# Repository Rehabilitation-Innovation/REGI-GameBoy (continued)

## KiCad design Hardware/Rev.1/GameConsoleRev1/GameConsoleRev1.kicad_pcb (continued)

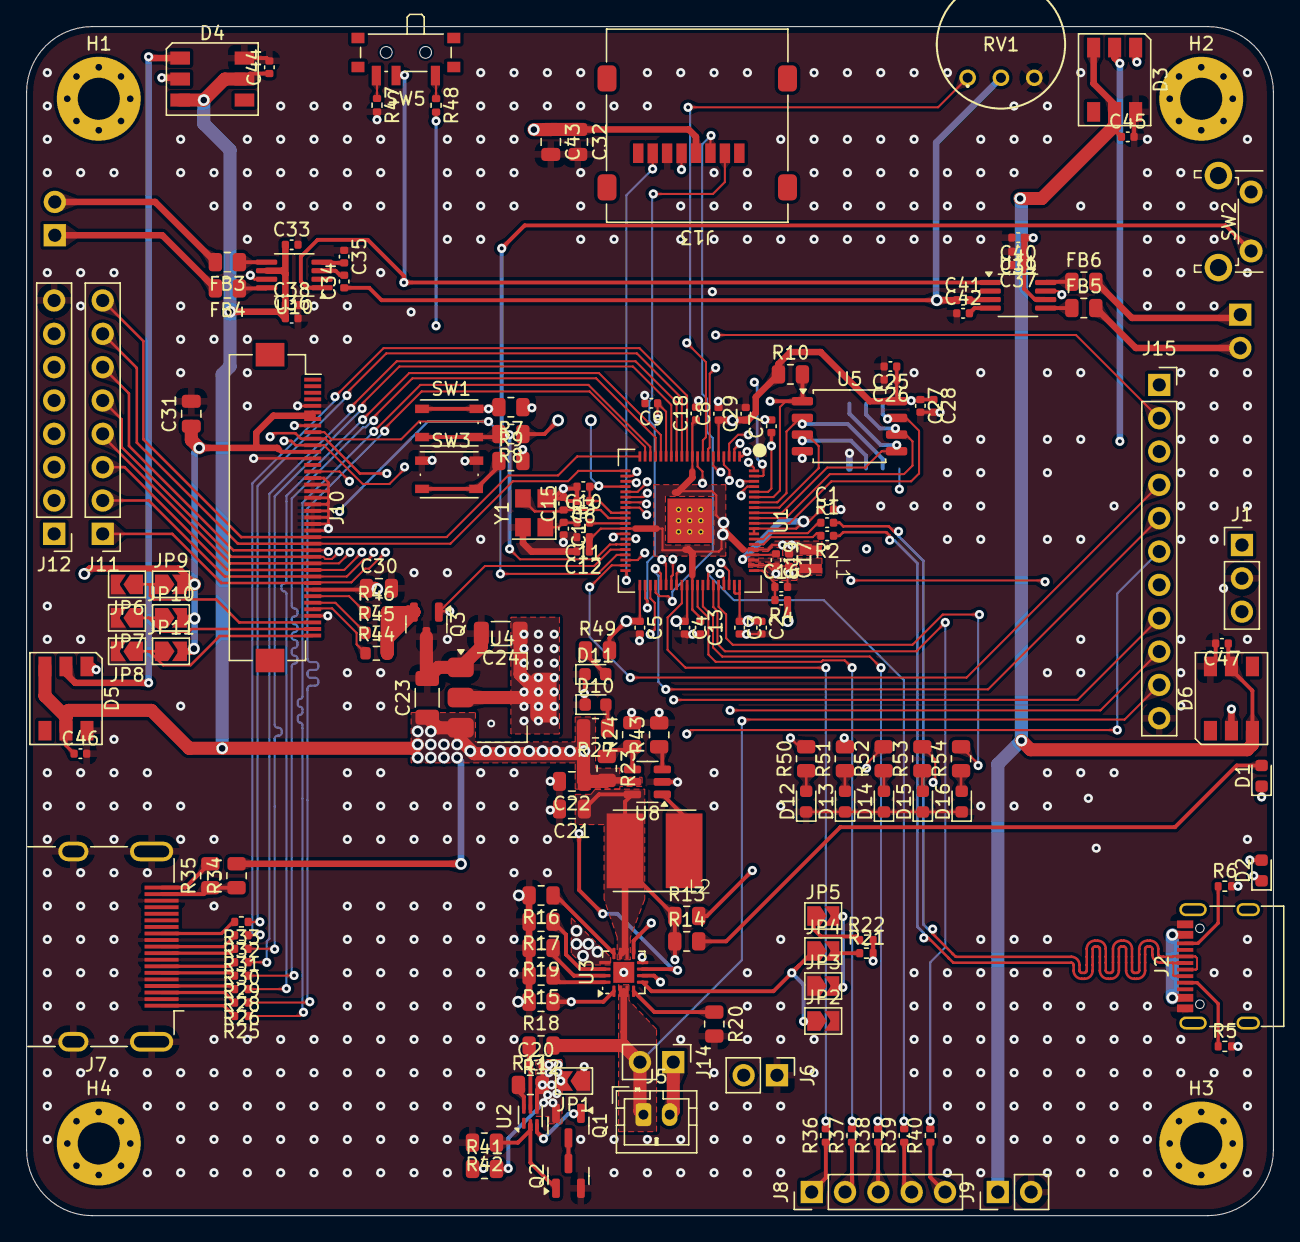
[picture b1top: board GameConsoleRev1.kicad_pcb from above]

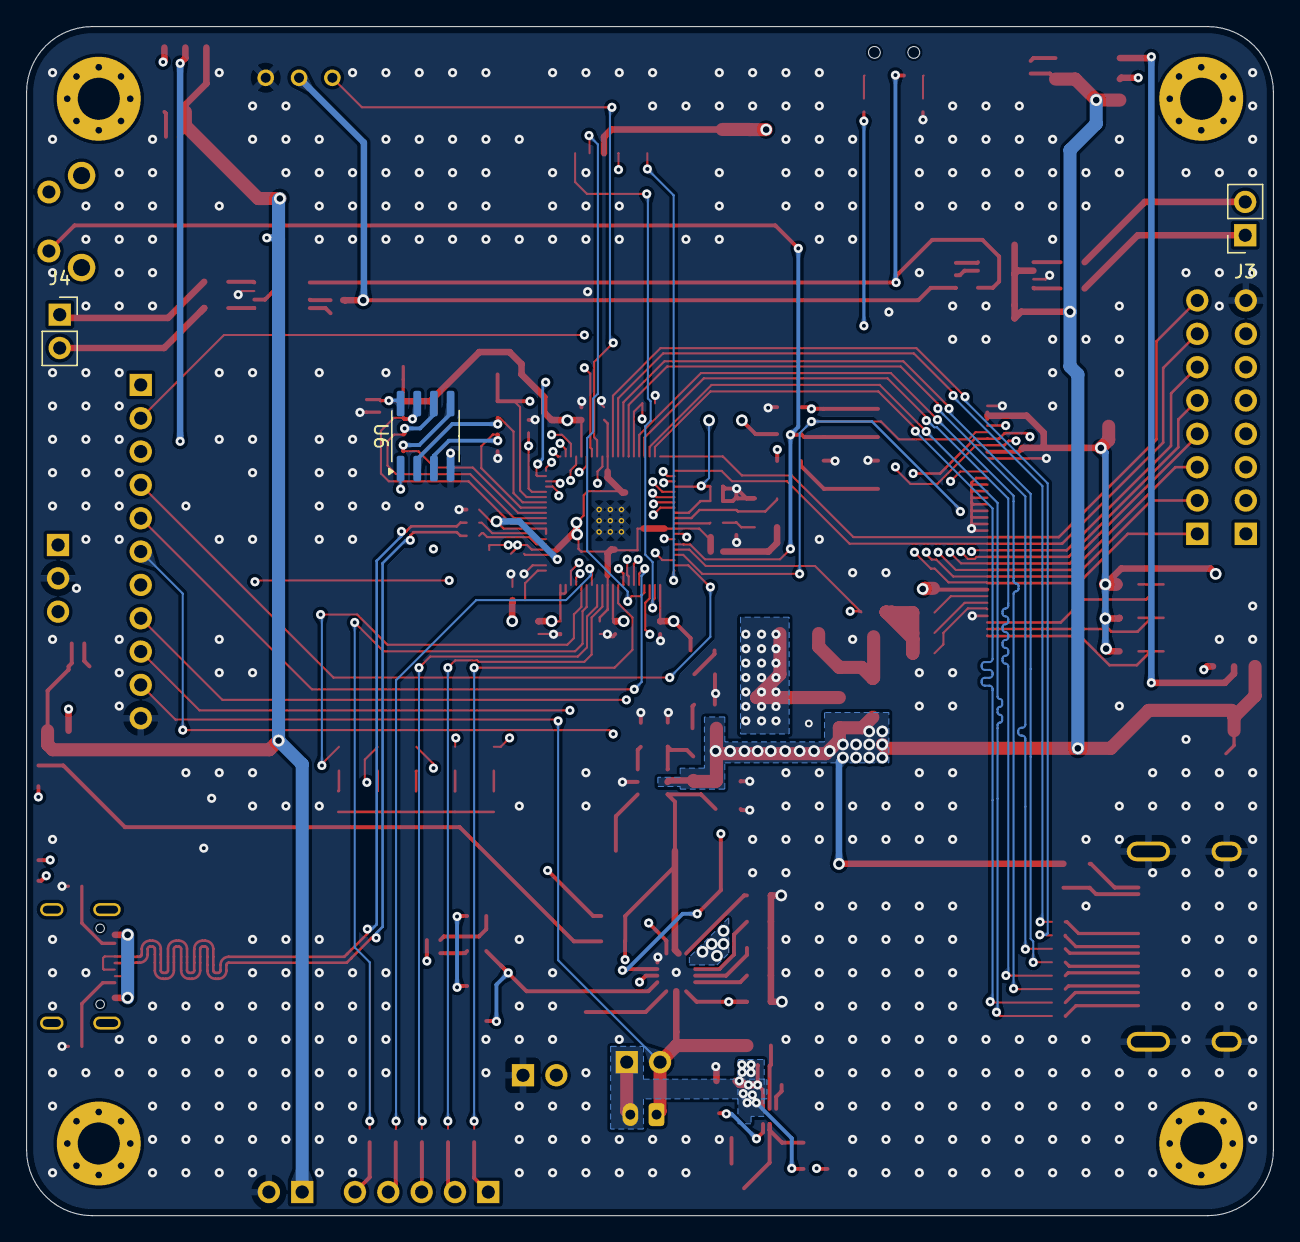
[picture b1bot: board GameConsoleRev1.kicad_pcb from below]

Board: 4 copper layers, 95.0 x 90.6 mm, 168 parts (3 on the bottom side), 147 nets.

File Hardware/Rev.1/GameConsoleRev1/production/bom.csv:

Designator,Footprint,Quantity,Value,LCSC Part #
"C1, C10, C11, C13, C18, C2, C20, C25, C27, C3, C36, C4, C40, C48, C5, C6, C7, C8, C9",0402,19,100n,C307331
"C12, C16, C17, C19, C29",0402,5,4u7,C23733
"C14, C15",0402,2,15p,C1548
C21,0805,1,10u,C15850
"C22, C30, C31, C32, C43",0805,5,22u,C45783
C23,1206,1,10u,C13585
C24,1206,1,22u,C12891
"C26, C28",0402,2,2u2,C12530
"C33, C34, C35, C37, C41, C42",0402,6,1u,C52923
"C38, C39, C44, C45, C46, C47",0402,6,10u,C15525
"D1, D10, D11",0603,3,BLUE,C965804
D12,0805,1,RED,C965804
"D13, D14",0805,2,GREEN,C965804
"D15, D16",0805,2,AMBER,C965804
D2,0603,1,AMBER,C965804
"D3, D4, D5, D6",LED_WS2812B_PLCC4_5.0x5.0mm_P3.2mm,4,WS2812,
"FB3, FB4, FB5, FB6",0805,4,600R@100MHz,C1017
J1,PinHeader_1x03_P2.54mm_Vertical,1,SWD-DAPLink,
J10,Hirose_FH12-40S-0.5SH_1x40-1MP_P0.50mm_Horizontal,1,Conn_01x40,C19273935
"J11, J12",PinHeader_1x08_P2.54mm_Vertical,2,Conn_01x08_Pin,
J13,microSD_HC_Molex_47219-2001,1,Micro_SD_Card,
J14,PinHeader_1x02_P2.54mm_Vertical,1,Through Hole,
J15,PinSocket_1x11_P2.54mm_Vertical,1,Conn_01x09_Pin,
J2,USB_C_Receptacle_G-Switch_GT-USB-7010ASV,1,USB_C_Receptacle_USB2.0_14P,C2988369
J3,PinSocket_1x02_P2.54mm_Vertical,1,L Channel,
J4,PinSocket_1x02_P2.54mm_Vertical,1,R Channel,
J5,JST_PH_B2B-PH-K_1x02_P2.00mm_Vertical,1,JST,
J6,PinHeader_1x02_P2.54mm_Vertical,1,Pack Temp,
J7,HDMI_A_Molex_208658-1001_Horizontal,1,HDMI_A,C720616
J8,PinHeader_1x05_P2.54mm_Vertical,1,Inputs,
J9,PinHeader_1x02_P2.54mm_Vertical,1,Button Pulls,
"JP1, JP10, JP11, JP2, JP3, JP4, JP5, JP6, JP7, JP8, JP9",SolderJumper-2_P1.3mm_Open_TrianglePad1.0x1.5mm,11,Jumper_2_Open,
L1,AOTA-B201610S3R3-101-T,1,3u3,C42411119
L2,"Ceaiya SMD,6x6mm CR6028-2R2N",1,2u2,C520367
"Q1, Q2",SOT-23,2,NMOS,C427390
Q3,SOT-23,1,NTR1P02T1G,C129192
"R1, R2",0603,2,27R,
"R10, R18, R35",0805,3,10k,C17414
R11,0805,1,2k2,C17520
R12,0805,1,330R,C17630
"R13, R14, R15, R16, R19, R20, R27, R49, R50, R51, R52, R53, R54, R7, R9",0805,15,1k,C17513
R17,0805,1,47k,C17713
"R21, R22, R36, R37, R38, R39, R40, R47, R48, R55, R56, R57, R59, R60",0402,14,10k,C25744
R23,0805,1,15k,C17475
R24,0805,1,4k7,C17673
"R25, R26, R28, R29, R30, R31, R32, R33",0402,8,220R,C25091
R3,0402,1,1k,C11702
"R34, R8",0805,2,10k,
R4,0402,1,33R,C25105
"R41, R42",0805,2,5M1,
R43,0805,1,100k,C149504
"R44, R45, R46",0603,3,2R,C22977
"R5, R6",0402,2,5k1,C25905
R58,0402,1,20k,C25765
RV1,RES3_91A_TTE,1,R_Potentiometer,
SW1,SW_Push_1P1T_NO_Vertical_Wuerth_434133025816,1,NRST,C2681476
SW2,SW_Tactile_SPST_Angled_PTS645Vx58-2LFS,1,NRST,
SW3,SW_Push_1P1T_NO_Vertical_Wuerth_434133025816,1,BOOTSEL,C2681476
"SW7, SW8",SW_Slide_SPDT_Angled_CK_OS102011MA1Q,2,SW_SPDT,
U1,RP2350B_QFN-80_EP_10.573x10.573_Pitch0.4mm,1,RP2350B-QFN80,C42415655
"U10, U11",MSOP-8_3x3mm_P0.65mm,2,PAM8302AAS,C113367
U2,WSON-6_1.5x1.5mm_P0.5mm,1,BQ29700DSER,C183096
U3,VQFN-16-1EP_3x3mm_P0.5mm_EP1.6x1.6mm,1,BQ24073RGT,C15220
U4,SOT-223-3_TabPin2,1,AMS1117-3.3,C6186
U5,SOIC-8_5.3x5.3mm_P1.27mm,1,W25Q128JVS,C97521
U6,SOIC-8_3.9x4.9mm_P1.27mm,1,ESP-PSRAM64,
U7,SOIC-8_3.9x4.9mm_P1.27mm,1,MCP6002-xSN,
U8,SOT-23-6,1,TLV61070ADBV,C6881375
Y1,Crystal_SMD_3225-4Pin_3.2x2.5mm,1,ABM8-272-T3 [12MHz],C20625731

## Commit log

2025-05-14 Done pseudo engine, will make first game and try overclock
2025-05-15 Fixed random pixel issue by adding set rotation 0
2025-05-15 Set rotation caused color inversion on st7735 blue pcb green tab. I added #define ST7735_MADCTL_BGR 0x08 to balbok lib to fix. and this is used instead of the rbg in the set rotation
2025-05-22 Fixed no time out and play again. added gui support for no time out
2025-06-05 Fixed DVi and rendering with pixel doubling and double buffering at 315MHz will add new files after this commit. This is just a back up one of a working example with no pixel doubling. Unverified
2025-06-05 I think the game engine is in a shippable state. I have the HSTX DVi stable. I will now make pcb. this commit is running single core with hstx dvi stable. It is capable of running 500 balls at once a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
2025-06-06 Got sprite Rendering working
2025-06-06 Added batch rendering for sprites, there is a memory leak some where and too many sprites cause crashes, or the core is too busy for inturrupts. I think multicore rendering is required for large spri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
2025-06-27 Added sprites
2025-07-08 Added CPP Build
2025-07-09 Removed cpp lib and tried using the C lib but no luck, will copy adafruit to see if it works
2025-07-09 Got the CPP Vsync working, realized this only works on some monitors because of the timings.
2025-07-11 Used chat gpt im not proud
2025-07-14 Implemented input event handling in the core engine and cleaned up globals
2025-07-21 Finished Dino Game
2025-07-21 Just made the pcb and flashed it; Worked first try
2025-08-05 Fixed broken submodule
2025-08-07 Made pong
2025-08-22 Cleaned folders and added 2player pong
2025-08-26 Created docs and added empty doxyfile
2025-08-26 Deleted uneccessary copies
2025-08-26 Added initial doxy files
2025-08-26 renamed html to docs
2025-08-27 Added more docs
2025-12-01 Dino Game
    Changes to scoring and score textbox. Added GPIO3 as home button
2025-12-04 Pong Updates Tentative
2025-12-04 Revert "Pong Updates Tentative"
    This reverts commit 9c0858d2b02bda978a9a0c0057800d11f0e39533.
2025-12-04 Pong1P - Dec 4
    - home button
    - Scoreboard titles
2025-12-05 Pong1P - Dec 5
    -Changed how score and highscore are counted
2025-12-05 Paddle-ball glitch fix
    Fixed the issue of the ball glitching and bouncing back and forth when it hits the top edge of the paddle.
2025-12-09 2P Pong
    Editing the code for 1P pong and commenting which codes to comment in/out to swap between one player and 2 player pong
2025-12-19 Paddle-ball glitch and 2P pong
    Fixed the issue of the ball glitching and bouncing back and forth when it hits the top edge of the paddle.
    Also made pong swappable between a 1P and 2P option
